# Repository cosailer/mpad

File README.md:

# mpad
**>> info**\
a 12 key macropad designed with atmega32u4, compatible with QMK, which is built with **virtser** and **I2C** enabled. the virtual serial port is used to control the 12 onboard backlight led, the I2C bus has a gesture sensor APDS-9960 connected to detect hand movement direction(up/down/left/right/near/far), proximity and light intensity. there is also a mouse encoder mounted.

**>> files**\
**mpad** :KiCad design files\
**qmk_firmware\keyboards\mpad** : firmware source for qmk build system\
**mpad.py** : a python test script to control the backlight LED via serial port\
**register_dump.txt** : an example register dump for APDS-9960

**>> setup**\
1, pin assignment, left: key and matrix assignment, right: backlight pin assignment
```
        D5     D4     D6       0,F5
     ┌──────┬──────┬──────┐
  B4 │ ESC  │ CALC │ MYCM │    1,B2   2,B1   3,B0
     ├──────┼──────┼──────┤
  B5 │ Ctl+C│ DEL  │ BSPC │    4,B3   5,F6   6,E6
     ├──────┼──────┼──────┤
  B6 │ SPACE│  Up  │  ENT │    7,F7   8,D7   9,F4
     ├──────┼──────┼──────┤
  B7 │ Left │ Down │ Right│   10,C6  11,C7  12,E2
     └──────┴──────┴──────┘
```

2, the onboard gesture sensor APDS-9960 is installed horizontally, the down movement is mapped to left key, up => right key, left => up key, right => down key

3, the 12 key individual backlight(single color) can be controlled from PC or mcu directly, allows it to be a LED notification light

the communication protocol: (each [xx] corresponds to 1 byte)
```
cmd 1: [0xAA] [ B1 ] [ B2 ] [0xE1] : set back light   ACK 1:[0xE1] ['\n']
cmd 2: [0xAA] [0xE2] : request timer                  ACK 2:[0xE2] [ T1 ] [ T2 ] [ T3 ] [ T4 ] ['\n']
cmd 3: [0xAA] [0xE3] : request voltage                ACK 3:[0xE3] [ U1 ] [ U2 ] ['\n']
cmd 4: [0xAA] [0xE4] : request die_temp               ACK 4:[0xE4] [ D1 ] [ D2 ] ['\n']
cmd 5: [0xAA] [0xE5] : request proximity              ACK 5:[0xE5] [ P1 ] ['\n']
cmd 6: [0xAA] [0xE6] : request light                  ACK 6:[0xE6] [ L1 ] [ L2 ] ['\n']
```
the script **mpad.py** sends commands to mpad every 100ms, to control the backlight LED and request some other system information. 

4, an onboard mouse encoder is mapped to volume control, which can be controlled via one finger

**>> PCB**\
the PCB is designed with KiCad 7.07. with the addition of an encoder, the PCB height size has grown over the 100mm. a small daughter board is attached to mount the gesture sensor and the encoder, the daughter board also has some extra room to mount other I2C sensors.

**>> notes**\
1, even with interrupt enabled, the driver for the APDS-9960 still needs hundreds of milliseconds to measure/calculate the direction of the movements, during this time the keypad will not respond to other inputs, this is the limitation of the sensor.

2, apart from normal movement direction detection, another gesture is also possible: **proximity tap** within a predfined time window (e.g. 1.5 seconds), it could be one tap, two taps or more taps. but proximity tap cannot be enabled togethe with the normal gesture detection.

3, the APDS-9960 interrupt is active low.

4, the serial port in qmk running on atmega32u4 can only process the received data one byte a time, so that it does not block normal keyboard functions.

**>> refernces**\
1, https://qmk.fm \
2, https://github.com/njeff/cherryblossom \
3, https://www.broadcom.com/products/optical-sensors/integrated-ambient-light-and-proximity-sensors/apds-9960 \
4, https://learn.sparkfun.com/tutorials/apds-9960-rgb-and-gesture-sensor-hookup-guide/all

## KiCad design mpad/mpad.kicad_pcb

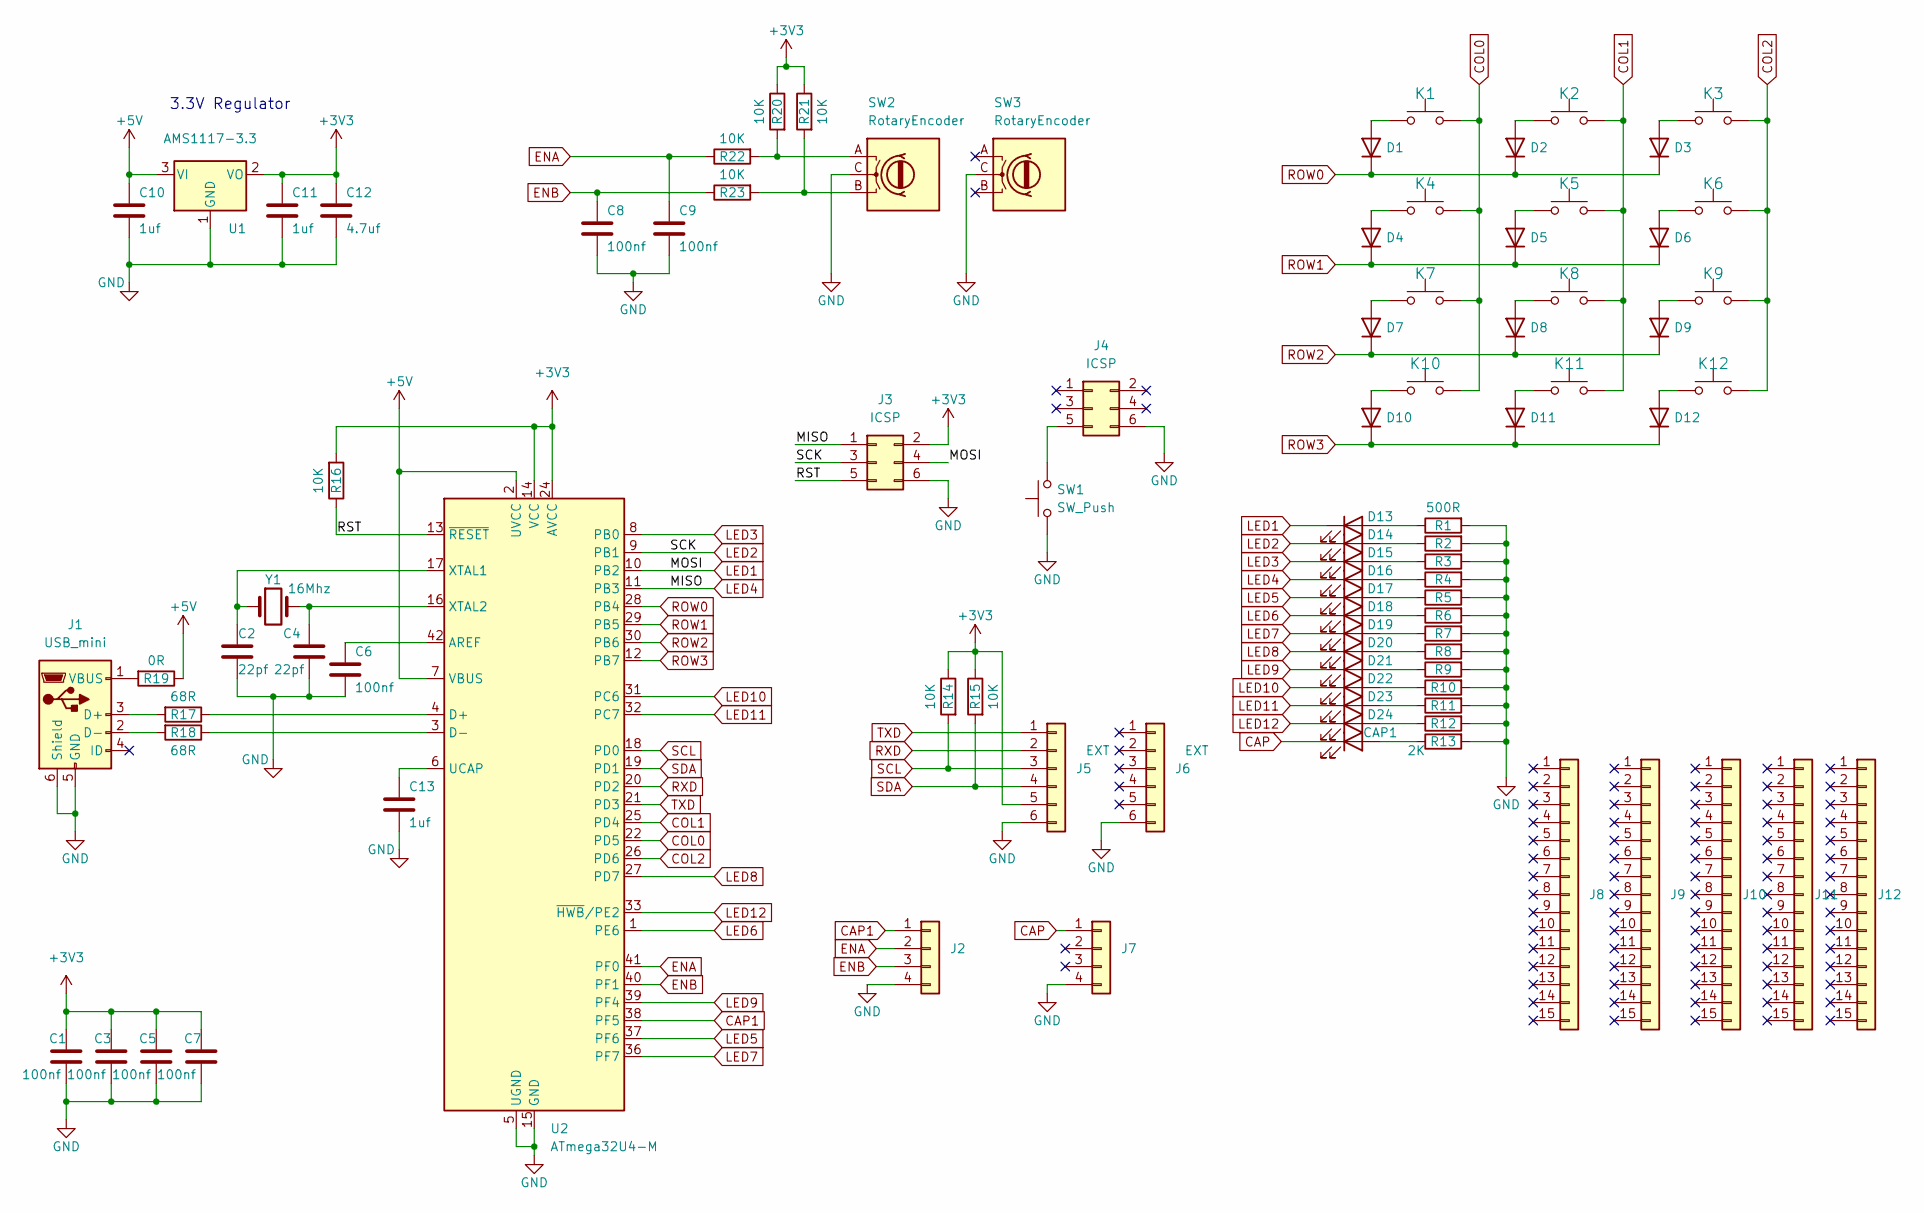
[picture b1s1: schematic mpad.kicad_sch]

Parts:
C1, C3, C5, C6, C7, C8, C9: 100nf; C_0603_1608Metric_Pad1.08x0.95mm_HandSolder
C2, C4: 22pf; C_0603_1608Metric_Pad1.08x0.95mm_HandSolder
C10, C11, C13: 1uf; C_0603_1608Metric_Pad1.08x0.95mm_HandSolder
C12: 4.7uf; C_0603_1608Metric_Pad1.08x0.95mm_HandSolder
CAP1: LED; LED_0603_1608Metric_Pad1.05x0.95mm_HandSolder
D1, D2, D3, D4, D5, D6, D7, D8, D9, D10, D11, D12: D; D_MiniMELF
D13, D14, D15, D16, D17, D18, D19, D20, D21, D22, D23, D24: LED; LED_0603_1608Metric_Pad1.05x0.95mm_HandSolder
J1: USB_mini; USB_Mini-B_Wuerth_65100516121_Horizontal
J2, J7: Status; PinHeader_1x04_P2.54mm_Vertical
J3, J4: ICSP; PinHeader_2x03_P2.54mm_Vertical
J5, J6: EXT; PinHeader_1x06_P2.54mm_Vertical
J8, J9, J10, J11, J12: UART; PinHeader_1x15_P2.54mm_Vertical
K1, K2, K3, K4, K5, K6, K7, K8, K9, K10, K11, K12: KEYSW; SW_MX
R1, R2, R3, R4, R5, R6, R7, R8, R9, R10, R11, R12: 500R; R_0603_1608Metric_Pad0.98x0.95mm_HandSolder
R13: 2K; R_0603_1608Metric_Pad0.98x0.95mm_HandSolder
R14, R15, R16, R20, R21, R22, R23: 10K; R_0603_1608Metric_Pad0.98x0.95mm_HandSolder
R17, R18: 68R; R_0603_1608Metric_Pad0.98x0.95mm_HandSolder
R19: 0R; R_0603_1608Metric_Pad0.98x0.95mm_HandSolder
SW1: SW_Push; SW_SPST_Omron_B3FS-100xP
SW2, SW3: RotaryEncoder; RotaryEncoder_Bourns_Horizontal_PEC12R-2xxxF-Nxxxx
U1: AMS1117-3.3; SOT-223-3_TabPin2
U2: ATmega32U4-M; QFN-44-1EP_7x7mm_P0.5mm_EP5.15x5.15mm_no_pad
Y1: 16Mhz; Crystal_HC18-U_Vertical

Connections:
+3V3: C1.1, C3.1, C5.1, C7.1, C11.1, C12.1, J3.2, J5.5, R14.1, R15.1, R16.2, R20.1, R21.1, U1.2 (VO), U2.14 (VCC), U2.24 (AVCC), U2.34 (VCC), U2.44 (AVCC)
+5V: C10.1, R19.1, U1.3 (VI), U2.2 (UVCC), U2.7 (VBUS)
/RST: J3.5, R16.1, U2.13 (~RESET)
CAP: CAP1.1 (K), J7.1
CAP1: J2.1, U2.38 (PF5)
COL0: K1.2, K4.2, K7.2, K10.2, U2.22 (PD5)
COL1: K2.2, K5.2, K8.2, K11.2, U2.25 (PD4)
COL2: K3.2, K6.2, K9.2, K12.2, U2.26 (PD6)
ENA: C9.1, J2.2, R22.1, U2.41 (PF0)
ENB: C8.1, J2.3, R23.1, U2.40 (PF1)
GND: C1.2, C2.2, C3.2, C4.2, C5.2, C6.2, C7.2, C8.2, C9.2, C10.2, C11.2, C12.2, C13.2, J1.5 (GND), J1.6 (Shield), J2.4, J3.6, J4.6, J5.6, J6.6, J7.4, R1.2, R2.2, R3.2, R4.2, R5.2, R6.2, R7.2, R8.2, R9.2, R10.2, R11.2, R12.2, R13.2, SW1.1, SW2.C, SW3.C, U1.1 (GND), U2.5 (UGND), U2.15 (GND), U2.23 (GND), U2.35 (GND), U2.43 (GND)
LED1: D13.1 (K), J3.4, U2.10 (PB2)
LED2: D14.1 (K), J3.3, U2.9 (PB1)
LED3: D15.1 (K), U2.8 (PB0)
LED4: D16.1 (K), J3.1, U2.11 (PB3)
LED5: D17.1 (K), U2.37 (PF6)
LED6: D18.1 (K), U2.1 (PE6)
LED7: D19.1 (K), U2.36 (PF7)
LED8: D20.1 (K), U2.27 (PD7)
LED9: D21.1 (K), U2.39 (PF4)
LED10: D22.1 (K), U2.31 (PC6)
LED11: D23.1 (K), U2.32 (PC7)
LED12: D24.1 (K), U2.33 (~HWB/PE2)
unnamed: CAP1.2 (A), R13.1
unnamed: D1.2 (A), K1.1
unnamed: D2.2 (A), K2.1
unnamed: D3.2 (A), K3.1
unnamed: D4.2 (A), K4.1
unnamed: D5.2 (A), K5.1
unnamed: D6.2 (A), K6.1
unnamed: D7.2 (A), K7.1
unnamed: D8.2 (A), K8.1
unnamed: D9.2 (A), K9.1
unnamed: D10.2 (A), K10.1
unnamed: D11.2 (A), K11.1
unnamed: D12.2 (A), K12.1
unnamed: D13.2 (A), R1.1
unnamed: D14.2 (A), R2.1
unnamed: D15.2 (A), R3.1
unnamed: D16.2 (A), R4.1
unnamed: D17.2 (A), R5.1
unnamed: D18.2 (A), R6.1
unnamed: D19.2 (A), R7.1
unnamed: D20.2 (A), R8.1
unnamed: D21.2 (A), R9.1
unnamed: D22.2 (A), R10.1
unnamed: D23.2 (A), R11.1
unnamed: D24.2 (A), R12.1
unnamed: J1.3 (D+), R17.2
unnamed: J1.2 (D-), R18.2
unnamed: J1.1 (VBUS), R19.2
unnamed: J4.5, SW1.2
unnamed: R20.2, R22.2, SW2.A
unnamed: R21.2, R23.2, SW2.B
unnamed: C6.1, U2.42 (AREF)
unnamed: R17.1, U2.4 (D+)
unnamed: R18.1, U2.3 (D-)
unnamed: C13.1, U2.6 (UCAP)
unnamed: C2.1, U2.17 (XTAL1), Y1.1
unnamed: C4.1, U2.16 (XTAL2), Y1.2
ROW0: D1.1 (K), D2.1 (K), D3.1 (K), U2.28 (PB4)
ROW1: D4.1 (K), D5.1 (K), D6.1 (K), U2.29 (PB5)
ROW2: D7.1 (K), D8.1 (K), D9.1 (K), U2.30 (PB6)
ROW3: D10.1 (K), D11.1 (K), D12.1 (K), U2.12 (PB7)
RXD: J5.2, U2.20 (PD2)
SCL: J5.3, R14.2, U2.18 (PD0)
SDA: J5.4, R15.2, U2.19 (PD1)
TXD: J5.1, U2.21 (PD3)

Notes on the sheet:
3.3V Regulator

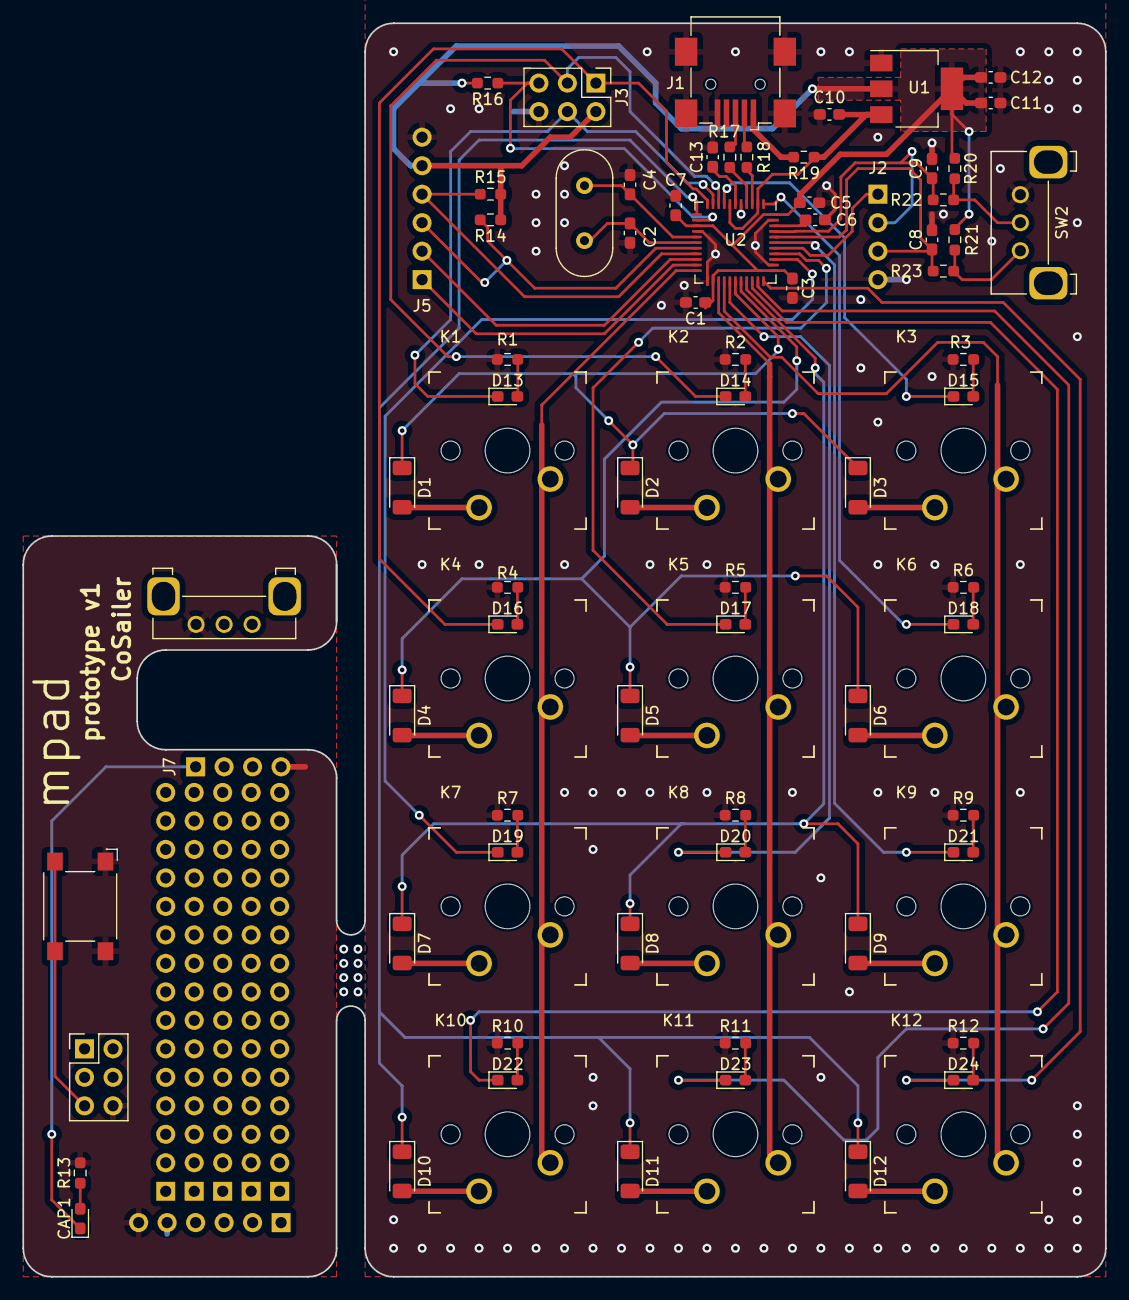
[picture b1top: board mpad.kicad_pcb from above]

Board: 2 copper layers, 96.5 x 111.7 mm, 91 parts (0 on the bottom side), 68 nets.

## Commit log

2023-10-21 add pcb files
2023-10-24 add qmk source
2023-10-24 add firmware hex
2023-10-24 add photos
